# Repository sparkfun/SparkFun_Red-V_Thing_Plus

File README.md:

SparkFun RED-V Thing Plus
========================================

*[SparkFun RED-V Thing Plus (DEV-15799)](https://www.sparkfun.com/products/15799)*

The SparkFun RED-V (pronounced “red-five”) Thing Plus is a low-cost, development board in our popular Thing Plus footprint and adds in the Freedom E310 core and RISC-V instruction set architecture (ISA). What sets the RED-V Thing Plus apart is the completely open-source approach from hardware to ISA. That means anyone can make full use the microcontroller without requiring royalties, licenses, or non-disclosure agreements.

It utilizes our handy Qwiic Connect System which means no soldering or shields are required to connect it to the rest of your system with plug-and-play I<sup>2</sup>C functionality. Since the Thing Plus footprint is also Feather-compatible, you can take advantage of a shield option in case you didn't want to use our Qwiic Connect System! Additionally, it comes programmed with a simple bootloader. The modern USB-C connector makes it easy to program via the FE310's NXP K22 ARM Cortex-M4 for USB connectivity and operating as a JTAG interface. For more advanced users who prefer to use the power and speed of professional tools, we've also exposed the JTAG connector.  With so much functionality, the SparkFun RED-V Thing Plus is an ideal choice for your RISC-V project.

The on board Freedom E310 (FE310) is the first member of the Freedom Everywhere family of customizable SoCs from SiFive. Designed for microcontroller, embedded, IoT, and wearable applications, the FE310 features SiFive’s E31 CPU Coreplex, a high-performance, 32-bit RV32IMAC core. Running at 320+ MHz, the FE310 is among the fastest microcontrollers in the market. Additional features include a 16KB L1 Instruction Cache, a 16KB Data SRAM scratchpad, hardware multiply/divide, a debug module, flexible clock generation with on-chip oscillators and PLLs, and a wide variety of peripherals including UARTs, QSPI, PWMs, and timers. Multiple power domains and a low-power standby mode ensure a wide variety of applications can benefit from the FE310. The RED-V Thing Plus requires Freedom Studio software or a Zephyr RTOS build environment set up to program the board and interface with it.

Repository Contents
-------------------

* **/Hardware** - Eagle design files (.brd, .sch)

Documentation
--------------

* **[Hookup Guide](https://learn.sparkfun.com/tutorials/red-v-redboard-hookup-guide)** - Basic hookup guide for the SparkFun RED-V Thing Plus.
* **[RED-V Development Guide](https://learn.sparkfun.com/tutorials/red-v-development-guide)** - Getting started with the RED-V in Freedom Studio and Zephyr RTOS.

License Information
-------------------

This product is _**open source**_! 

Please review the LICENSE.md file for license information. 

If you have any questions or concerns on licensing, please contact technical support on our [SparkFun forums](https://forum.sparkfun.com/viewforum.php?f=152).

Distributed as-is; no warranty is given.

- Your friends at SparkFun.

_<COLLABORATION CREDIT>_

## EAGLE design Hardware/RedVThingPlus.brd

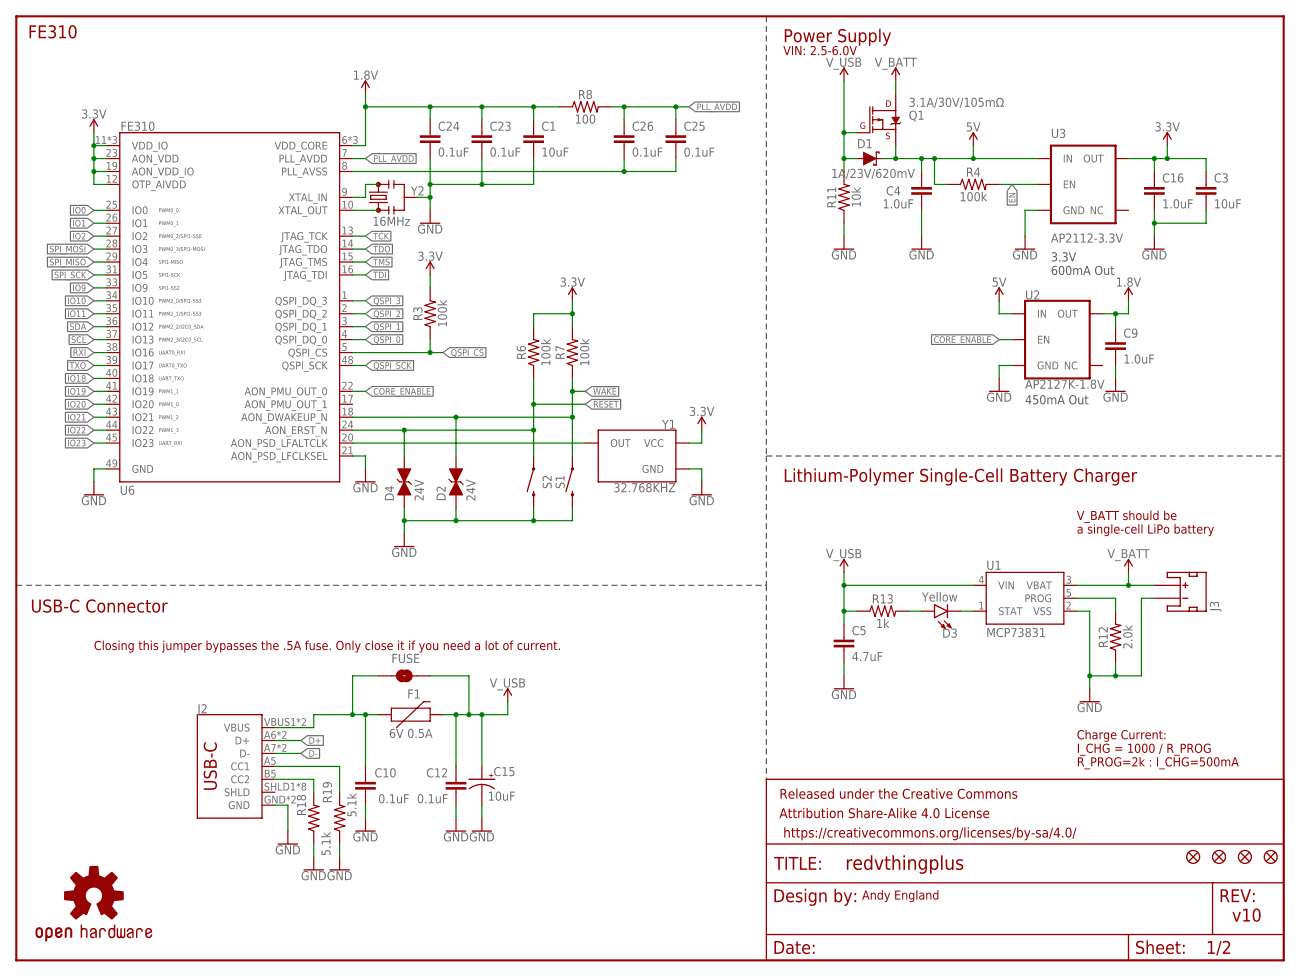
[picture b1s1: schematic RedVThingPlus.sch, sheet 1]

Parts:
C1, C3: 10uF; 0603
C4, C9, C16: 1.0uF; 0603
C5: 4.7uF; 0603
C10, C12, C23, C24, C25, C26: 0.1uF; 0603
C15: 10uF; EIA3216
D1: 1A/23V/620mV; SOD-323
D2, D4: 24V; 0603
D3: Yellow; LED-0603
F1: 6V 0.5A; 0805
FRAME2: FRAME-LETTER; CREATIVE_COMMONS
FUSE: JUMPER-SMT_2_NO_NO-SILK; SMT-JUMPER_2_NO_NO-SILK
J2: USB Female Type C Connector; USB-C-16P
J3: JST_2MM_MALE; JST-2-SMD
JP8, JP9, JP15, JP16: FIDUCIAL1X2; FIDUCIAL-1X2
Q1: 3.1A/30V/105mΩ; SOT23-3
R3, R4, R6, R7: 100k; 0603
R8: 100; 0603
R11: 10k; 0603
R12: 2.0k; 0603
R13: 1k; 0603
R18, R19: 5.1k; 0603
S1, S2: MOMENTARY-SWITCH-SPST-SMD-4.6X2.8MM; TACTILE_SWITCH_SMD_4.6X2.8MM
U1: MCP73831; SOT23-5
U2: AP2127K-1.8V; SOT23-5
U3: AP2112-3.3V; SOT23-5
U6: FE310; QFN-48-.4MMPITCH
U$16: OSHW-LOGOS; OSHW-LOGO-S
Y1: 32.768KHZ; CRYSTAL-SMD-2X1.2MM
Y2: 16MHz; RESONATOR-SMD-3.2X1.3

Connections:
1.8V: C1.1, C9.1, C23.1, C24.1, R8.1, U2.5 (OUT), U6.6 (VDD_CORE), U6.30 (VDD_CORE), U6.46 (VDD_CORE)
3.3V: C3.1, C16.1, R3.2, R6.2, R7.2, U3.5 (OUT), U6.11 (VDD_IO), U6.12 (OTP_AIVDD), U6.19 (AON_VDD_IO), U6.23 (AON_VDD), U6.32 (VDD_IO), U6.47 (VDD_IO), Y1.4 (VCC); also elsewhere on the board
5V: C4.1, D1.C, Q1.2 (S), R4.1, U2.1 (IN), U3.1 (IN)
!RESET: D4.2 (C), R6.1, S2.1, S2.2 (1), U6.24 (AON_ERST_N); also elsewhere on the board
!WAKE: D2.2 (C), R7.1, S1.1, S1.2 (1), U6.18 (AON_DWAKEUP_N)
CORE_ENABLE: U2.3 (EN), U6.22 (AON_PMU_OUT_0)
D+: J2.A6 (D+), J2.B6 (D+); also elsewhere on the board
D-: J2.A7 (D-), J2.B7 (D-); also elsewhere on the board
EN: R4.2, U3.3 (EN); also elsewhere on the board
GND: C1.2, C3.2, C4.2, C5.2, C9.2, C10.2, C12.2, C15.-, C16.2, C23.2, C24.2, D2.1 (A), D4.1 (A), J2.GND, J2.GND2 (GND), J3.1 (-), R11.1, R12.1, R18.1, R19.1, S1.3 (2), S1.4 (2), S2.3 (2), S2.4 (2), U1.2 (VSS), U2.2 (GND), U3.2 (GND), U6.21 (AON_PSD_LFCLKSEL), U6.49 (GND), Y1.2 (GND), Y2.2; also elsewhere on the board
IO0: U6.25 (IO0); also elsewhere on the board
IO1: U6.26 (IO1); also elsewhere on the board
IO2: U6.27 (IO2); also elsewhere on the board
IO9: U6.33 (IO9); also elsewhere on the board
IO10: U6.34 (IO10); also elsewhere on the board
IO11: U6.35 (IO11); also elsewhere on the board
IO18: U6.40 (IO18); also elsewhere on the board
IO19: U6.41 (IO19); also elsewhere on the board
IO20: U6.42 (IO20); also elsewhere on the board
IO21: U6.43 (IO21); also elsewhere on the board
IO22: U6.44 (IO22); also elsewhere on the board
IO23: U6.45 (IO23); also elsewhere on the board
unnamed: U6.10 (XTAL_OUT), Y2.1
unnamed: U6.9 (XTAL_IN), Y2.3
unnamed: U6.20 (AON_PSD_LFALTCLK), Y1.3 (OUT)
unnamed: R12.2, U1.5 (PROG)
unnamed: C25.2, C26.2, U6.8 (PLL_AVSS)
unnamed: D3.C, U1.1 (STAT)
unnamed: J2.B5 (CC2), R18.2
unnamed: D3.A, R13.2
unnamed: J2.A5 (CC1), R19.2
PLL_AVDD: C25.1, C26.1, R8.2, U6.7 (PLL_AVDD)
QSPI_0: U6.4 (QSPI_DQ_0); also elsewhere on the board
QSPI_1: U6.3 (QSPI_DQ_1); also elsewhere on the board
QSPI_2: U6.2 (QSPI_DQ_2); also elsewhere on the board
QSPI_3: U6.1 (QSPI_DQ_3); also elsewhere on the board
QSPI_CS: R3.1, U6.5 (QSPI_CS); also elsewhere on the board
QSPI_SCK: U6.48 (QSPI_SCK); also elsewhere on the board
RXI: U6.38 (IO16); also elsewhere on the board
SCL: U6.37 (IO13); also elsewhere on the board
SDA: U6.36 (IO12); also elsewhere on the board
SPI_MISO: U6.29 (IO4); also elsewhere on the board
SPI_MOSI: U6.28 (IO3); also elsewhere on the board
SPI_SCK: U6.31 (IO5); also elsewhere on the board
TCK: U6.13 (JTAG_TCK); also elsewhere on the board
TDI: U6.16 (JTAG_TDI); also elsewhere on the board
TDO: U6.14 (JTAG_TDO); also elsewhere on the board
TMS: U6.15 (JTAG_TMS); also elsewhere on the board
TXO: U6.39 (IO17); also elsewhere on the board
VUSB: C10.1, F1.1, FUSE.1, J2.VBUS1 (VBUS), J2.VBUS2 (VBUS)
V_BATT: J3.2 (+), Q1.3 (D), U1.3 (VBAT); also elsewhere on the board
V_USB: C5.1, C12.1, C15.+, D1.A, F1.2, FUSE.2, Q1.1 (G), R11.2, R13.1, U1.4 (VIN); also elsewhere on the board

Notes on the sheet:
Power Supply
FE310
USB-C Connector
Andy England
v10
3.3V 600mA Out
450mA Out
Closing this jumper bypasses the .5A fuse. Only close it if you need a lot of current.
Lithium-Polymer Single-Cell Battery Charger
V_BATT should be a single-cell LiPo battery
Charge Current: I_CHG = 1000 / R_PROG R_PROG=2k : I_CHG=500mA
VIN: 2.5-6.0V

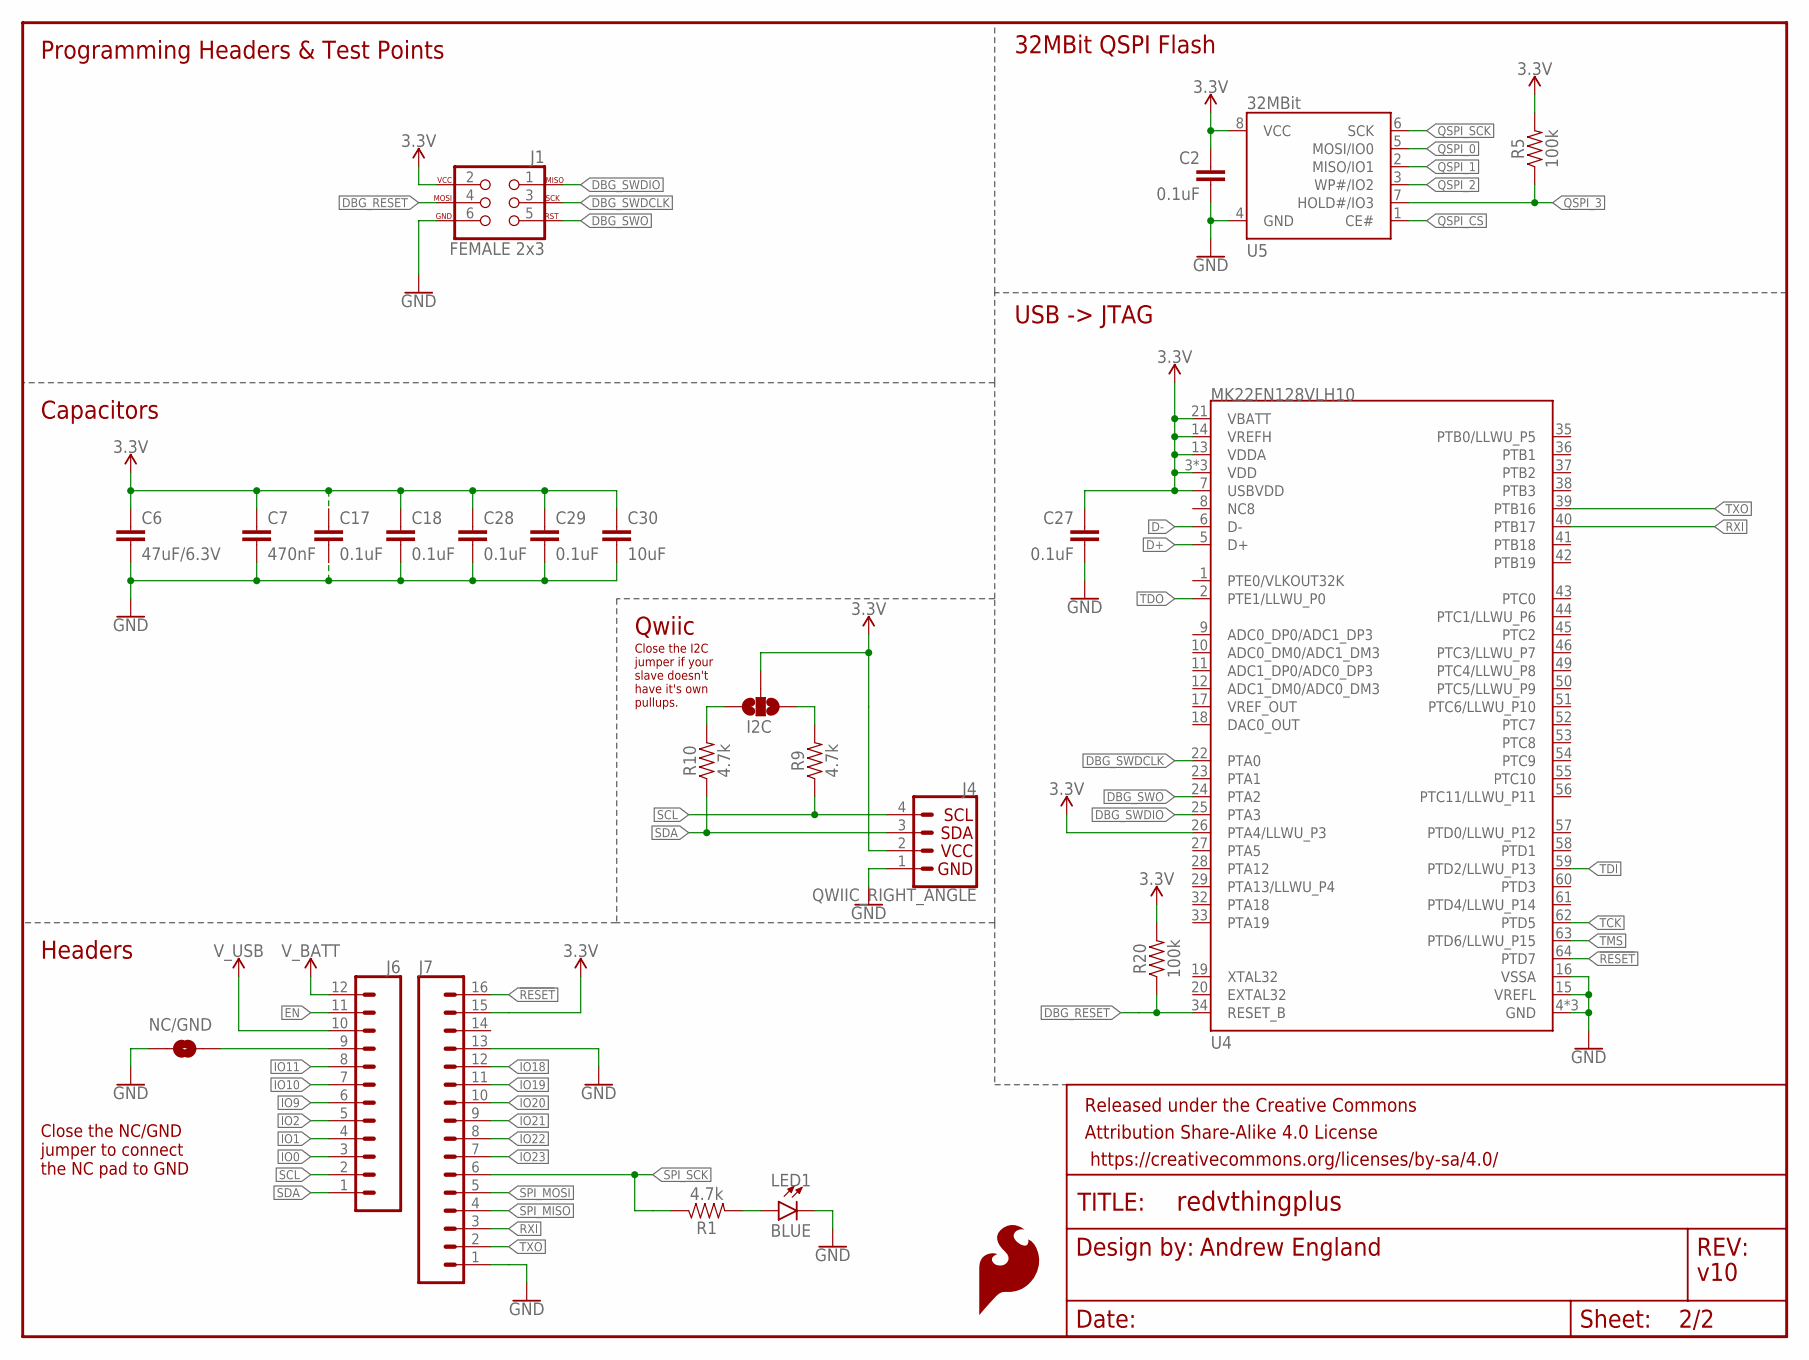
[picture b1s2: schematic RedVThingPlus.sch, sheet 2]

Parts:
C2, C17, C18, C27, C28, C29: 0.1uF; 0603
C6: 47uF/6.3V; 0805
C7: 470nF; 0603
C30: 10uF; 0603
FRAME1: FRAME-LETTER; CREATIVE_COMMONS
I2C: JUMPER-SMT_3_NO_NO-SILK; SMT-JUMPER_3_NO_NO-SILK
J1: FEMALE 2x3; 2X3_TEST_POINTS
J4: QWIIC_RIGHT_ANGLE; JST04_1MM_RA
J6: CONN_12SM_SQ_NO_SILK; 1X12_SM_SQ_NOSILK
J7: CONN_161X16_SM_SQ_NOSILK; 1X16_SM_SQ_NOSILK
LED1: BLUE; LED-0603
LOGO2: SFE_LOGO_FLAME.2_INCH; SFE_LOGO_FLAME_.2
NC/GND: JUMPER-SMT_2_NO_NO-SILK; SMT-JUMPER_2_NO_NO-SILK
R1, R9, R10: 4.7k; 0603
R5, R20: 100k; 0603
U4: MK22FN128VLH10; LQFP-64
U5: 32MBit; SO08

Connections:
3.3V: C2.1, C6.1, C7.1, C17.1, C18.1, C27.1, C28.1, C29.1, C30.1, I2C.2, J1.2, J4.2, J7.15, R5.2, R20.2, U4.3 (VDD), U4.7 (USBVDD), U4.13 (VDDA), U4.14 (VREFH), U4.21 (VBATT), U4.26 (PTA4/LLWU_P3), U4.30 (VDD), U4.48 (VDD), U5.8 (VCC); also elsewhere on the board
!RESET: J7.16, U4.64 (PTD7); also elsewhere on the board
D+: U4.5 (D+); also elsewhere on the board
D-: U4.6 (D-); also elsewhere on the board
DBG_RESET: J1.4, R20.1, U4.34 (RESET_B)
DBG_SWDCLK: J1.3, U4.22 (PTA0)
DBG_SWDIO: J1.1, U4.25 (PTA3)
DBG_SWO: J1.5, U4.24 (PTA2)
EN: J6.11; also elsewhere on the board
GND: C2.2, C6.2, C7.2, C17.2, C18.2, C27.2, C28.2, C29.2, C30.2, J1.6, J4.1, J7.1, J7.13, LED1.C, NC/GND.1, U4.4 (GND), U4.15 (VREFL), U4.16 (VSSA), U4.31 (GND), U4.47 (GND), U5.4 (GND); also elsewhere on the board
IO0: J6.3; also elsewhere on the board
IO1: J6.4; also elsewhere on the board
IO2: J6.5; also elsewhere on the board
IO9: J6.6; also elsewhere on the board
IO10: J6.7; also elsewhere on the board
IO11: J6.8; also elsewhere on the board
IO18: J7.12; also elsewhere on the board
IO19: J7.11; also elsewhere on the board
IO20: J7.10; also elsewhere on the board
IO21: J7.9; also elsewhere on the board
IO22: J7.8; also elsewhere on the board
IO23: J7.7; also elsewhere on the board
unnamed: LED1.A, R1.2
unnamed: J6.9, NC/GND.2
unnamed: I2C.1, R9.2
unnamed: I2C.3, R10.2
QSPI_0: U5.5 (MOSI/IO0); also elsewhere on the board
QSPI_1: U5.2 (MISO/IO1); also elsewhere on the board
QSPI_2: U5.3 (WP#/IO2); also elsewhere on the board
QSPI_3: R5.1, U5.7 (HOLD#/IO3); also elsewhere on the board
QSPI_CS: U5.1 (CE#); also elsewhere on the board
QSPI_SCK: U5.6 (SCK); also elsewhere on the board
RXI: J7.3, U4.40 (PTB17); also elsewhere on the board
SCL: J4.4, J6.2, R9.1; also elsewhere on the board
SDA: J4.3, J6.1, R10.1; also elsewhere on the board
SPI_MISO: J7.4; also elsewhere on the board
SPI_MOSI: J7.5; also elsewhere on the board
SPI_SCK: J7.6, R1.1; also elsewhere on the board
TCK: U4.62 (PTD5); also elsewhere on the board
TDI: U4.59 (PTD2/LLWU_P13); also elsewhere on the board
TDO: U4.2 (PTE1/LLWU_P0); also elsewhere on the board
TMS: U4.63 (PTD6/LLWU_P15); also elsewhere on the board
TXO: J7.2, U4.39 (PTB16); also elsewhere on the board
V_BATT: J6.12; also elsewhere on the board
V_USB: J6.10; also elsewhere on the board

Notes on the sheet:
Qwiic
Headers
Programming Headers & Test Points
32MBit QSPI Flash
Capacitors
Andrew England
v10
USB -> JTAG
Close the NC/GND jumper to connect the NC pad to GND
Close the I2C jumper if your slave doesn't have it's own pullups.

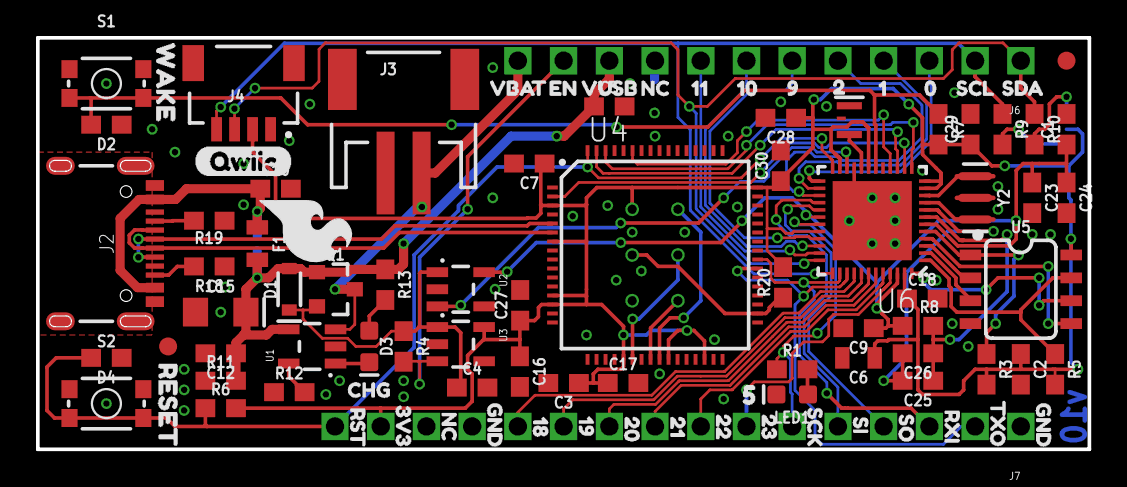
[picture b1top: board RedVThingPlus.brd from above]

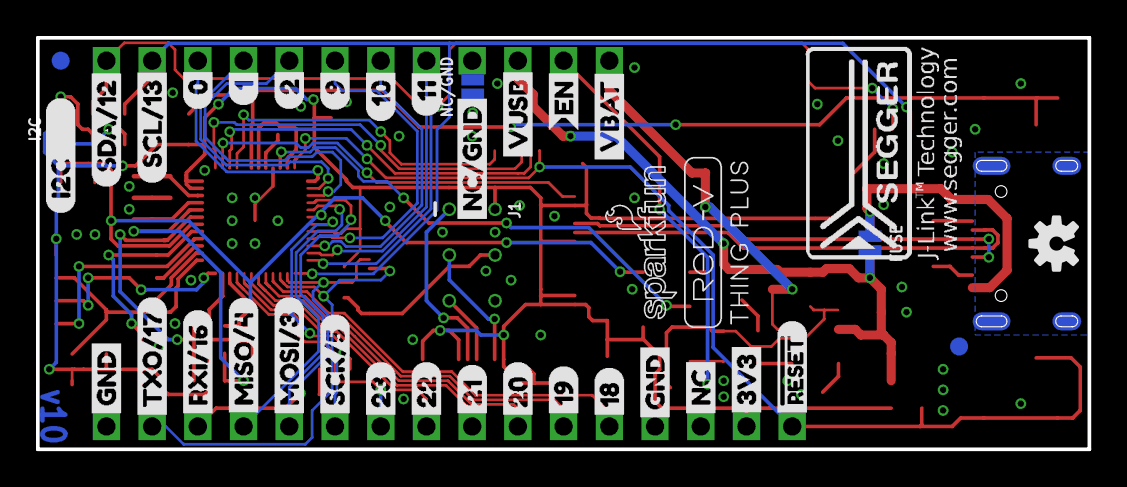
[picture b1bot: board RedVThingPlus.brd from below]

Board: 2 copper layers, 58.4 x 22.9 mm, 137 parts (40 on the bottom side), 60 nets.

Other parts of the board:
U$1: (QWIIC)
U$2: 96
U$3: 26
U$4: 15
U$5: 04
U$6: SDA9
U$8: TXO1
U$9: 107
U$11: 118
U$12: 1811
U$13: RED#V_THING_PLUS_BOARD_SILK#02#JPG
U$14: 1912
U$15: 2013
U$17: 2114
U$18: 2215
U$19: 2316
U$20: EN18
U$21, U$28: GND0
U$22, U$27: NC17
U$23: RXI2
U$24: SCK5
U$25: SCL10
U$26: VBAT19
U$29: #RESET34
U$30: 3V332
U$31: 3V333
U$32: 015
U$33: 114
U$34: 213
U$35: 912
U$36: 1011
U$37: 1110
U$38: CHG0
U$39: 1828
U$40: 1927
U$41: 2026
U$42: RED#V_THING_PLUS_BOARD_SILK#01#JPG
U$43: 2125
U$44: 2224
U$45: SEGGERLOGO#PNG
U$46: 50
U$47: 2323
U$48: EN8
U$49: ASDFKJGHB#JPG
U$50: I2C_______0
U$51, U$67: GND29
U$52: MISO#421
U$53: MOSI#320
U$54: NC#GND31
U$55: NC30
U$56: RST2
U$57: RXI#1619
U$58: SCK#522
U$59: SCL#1316
U$60: SDA#1217
U$61: SI0
U$62: SO1
U$63: TXO#1718
U$64: VBAT7
U$65: VUSB3
U$66: VUSB9
U$68: RESET1
U$69: WAKE0

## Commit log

2019-09-18 initial commit, schematic refactor from red-v
2019-09-20 all components placed, midway through routing
2019-09-24 initial layout complete, needs silk
2019-10-17 v10 changes for Reds design review
2019-10-18 post review changes
2019-10-22 post qc double check changes
2019-10-23 updating to final silk
2019-10-23 updating silk
2019-11-21 small silk update for release
2019-11-21 Update README.md and Unused folders
    Remove Unused folders and update the description for the RED-V Thing Plus
2019-12-10 updating to 100 Ohm resistor on R8

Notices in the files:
parts and their libraries:
SparkFun-Aesthetics: Licensing: CC v3.0 Share-Alike You are welcome to use this library for commercial purposes.
SparkFun-Aesthetics: Released under the Creative Commons Attribution Share-Alike 4.0 License
SparkFun-Aesthetics: https://creativecommons.org/licenses/by-sa/4.0
